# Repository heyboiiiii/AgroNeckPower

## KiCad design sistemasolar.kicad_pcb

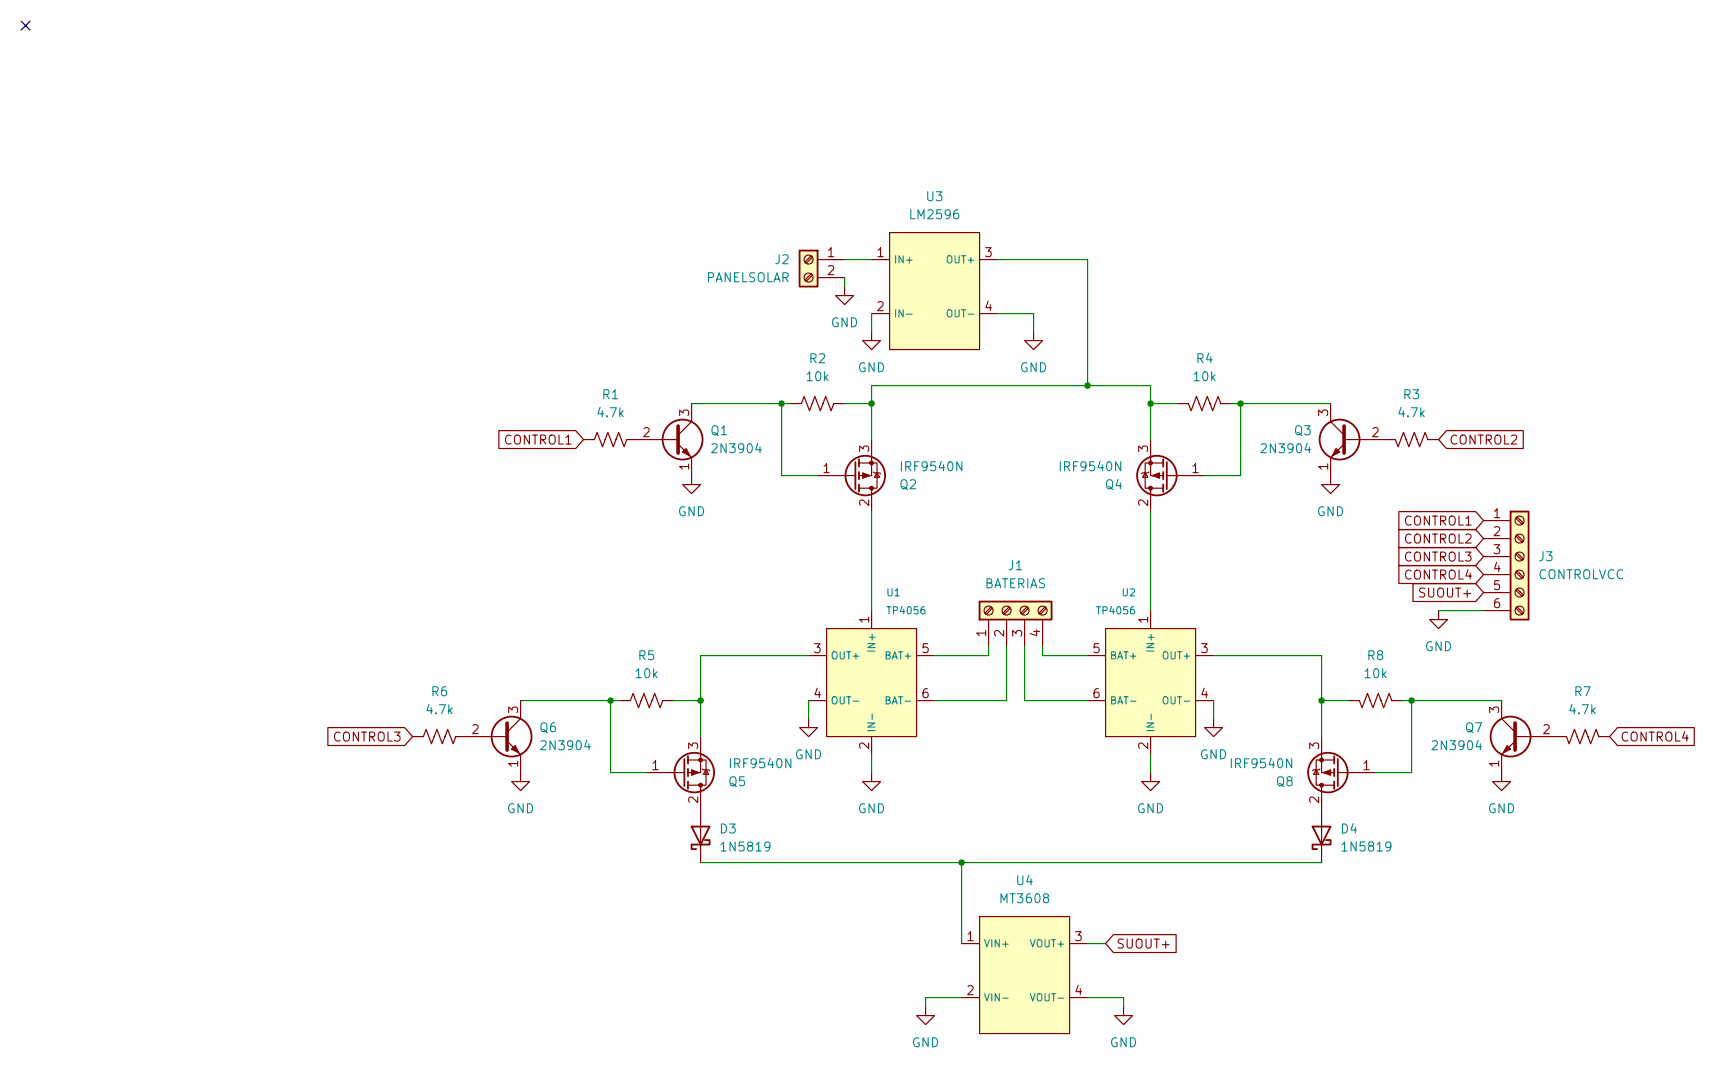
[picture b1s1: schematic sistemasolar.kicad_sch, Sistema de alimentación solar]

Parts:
D3, D4: 1N5819; D_DO-41_SOD81_P10.16mm_Horizontal
J1: BATERIAS; TerminalBlock_MaiXu_MX126-5.0-04P_1x04_P5.00mm
J2: PANELSOLAR; TerminalBlock_MaiXu_MX126-5.0-02P_1x02_P5.00mm
J3: CONTROLVCC; TerminalBlock_MaiXu_MX126-5.0-06P_1x06_P5.00mm
Q1, Q3, Q6, Q7: 2N3904; TO-92_Inline
Q2, Q4, Q5, Q8: IRF9540N; TO-220-3_Vertical
R1, R3, R6, R7: 4.7k; R_Axial_DIN0204_L3.6mm_D1.6mm_P7.62mm_Horizontal
R2, R4, R5, R8: 10k; R_Axial_DIN0204_L3.6mm_D1.6mm_P7.62mm_Horizontal
U1, U2: TP4056
U3: LM2596
U4: MT3608

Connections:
CONTROL1: J3.1, R1.1
CONTROL2: J3.2, R3.1
CONTROL3: J3.3, R6.1
CONTROL4: J3.4, R7.1
GND: J2.2, J3.6, Q1.1 (E), Q3.1 (E), Q6.1 (E), Q7.1 (E), U1.2 (IN-), U1.4 (OUT-), U2.2 (IN-), U2.4 (OUT-), U3.2 (IN-), U3.4 (OUT-), U4.2 (VIN-), U4.4 (VOUT-)
unnamed: D3.2 (A), Q5.2 (D)
unnamed: D3.1 (K), D4.1 (K), U4.1 (VIN+)
unnamed: D4.2 (A), Q8.2 (D)
unnamed: J1.1, U1.5 (BAT+)
unnamed: J1.2, U1.6 (BAT-)
unnamed: J1.3, U2.6 (BAT-)
unnamed: J1.4, U2.5 (BAT+)
unnamed: J2.1, U3.1 (IN+)
unnamed: Q1.2 (B), R1.2
unnamed: Q1.3 (C), Q2.1 (G), R2.1
unnamed: Q2.2 (D), U1.1 (IN+)
unnamed: Q2.3 (S), Q4.3 (S), R2.2, R4.2, U3.3 (OUT+)
unnamed: Q3.2 (B), R3.2
unnamed: Q3.3 (C), Q4.1 (G), R4.1
unnamed: Q4.2 (D), U2.1 (IN+)
unnamed: Q5.1 (G), Q6.3 (C), R5.1
unnamed: Q5.3 (S), R5.2, U1.3 (OUT+)
unnamed: Q6.2 (B), R6.2
unnamed: Q7.2 (B), R7.2
unnamed: Q7.3 (C), Q8.1 (G), R8.1
unnamed: Q8.3 (S), R8.2, U2.3 (OUT+)
SUOUT+: J3.5, U4.3 (VOUT+)

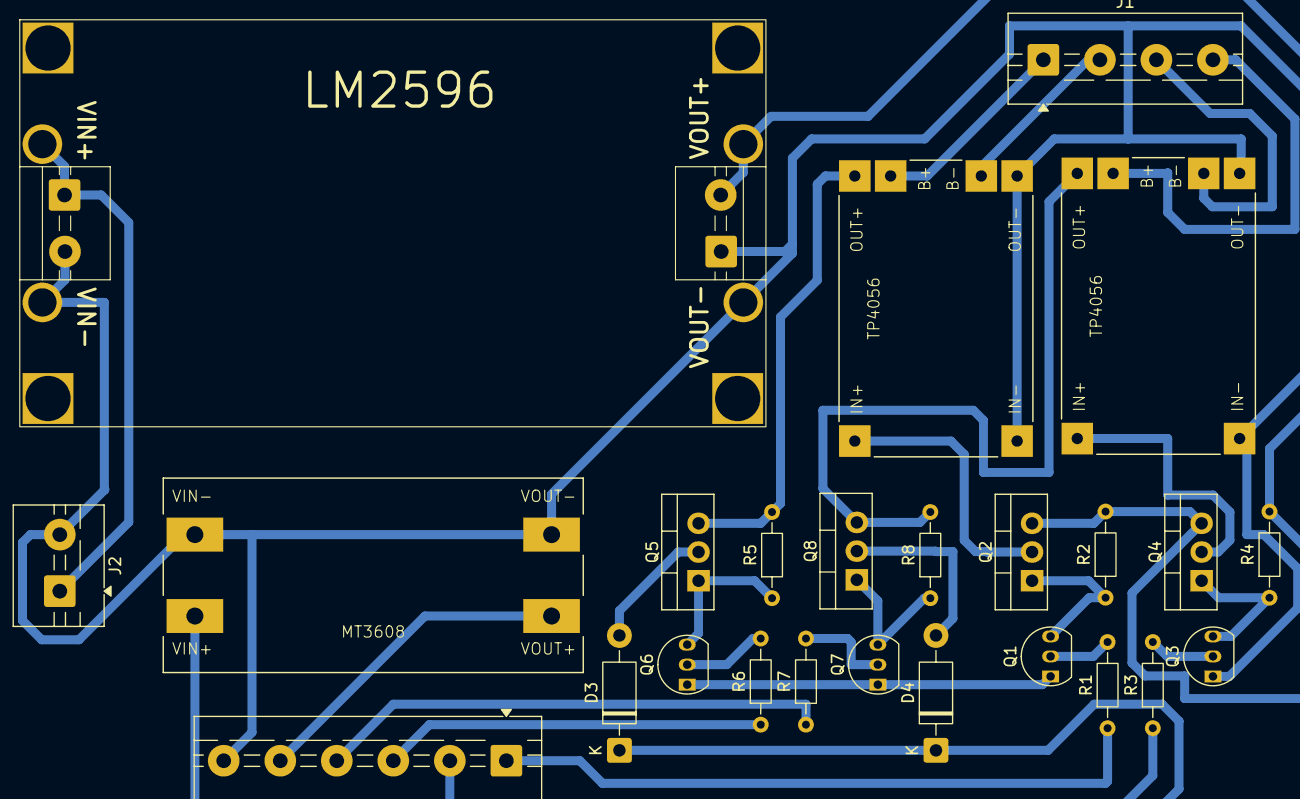
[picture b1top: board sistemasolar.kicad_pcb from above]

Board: 2 copper layers, 25 parts (0 on the bottom side), 27 nets.

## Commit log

2026-05-19 old files eliminated
2026-05-28 initial development of the Solar System(without 3d models)
2026-06-02 AgroneckPower finalizado
